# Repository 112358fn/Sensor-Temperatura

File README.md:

Sensor-Temperatura
==================

Medicion de temperatura mediante LM35 y PIC18F

Software:
=================
EAGLE
Version 7.1.0 for Linux
Light Edition
Freeware license for "non-profit"
and evaluation purposes

eagle-diff

Documentacion:
==================
Los datasheets de los componentes utilizados se encuentran en 
el directorio Doc/

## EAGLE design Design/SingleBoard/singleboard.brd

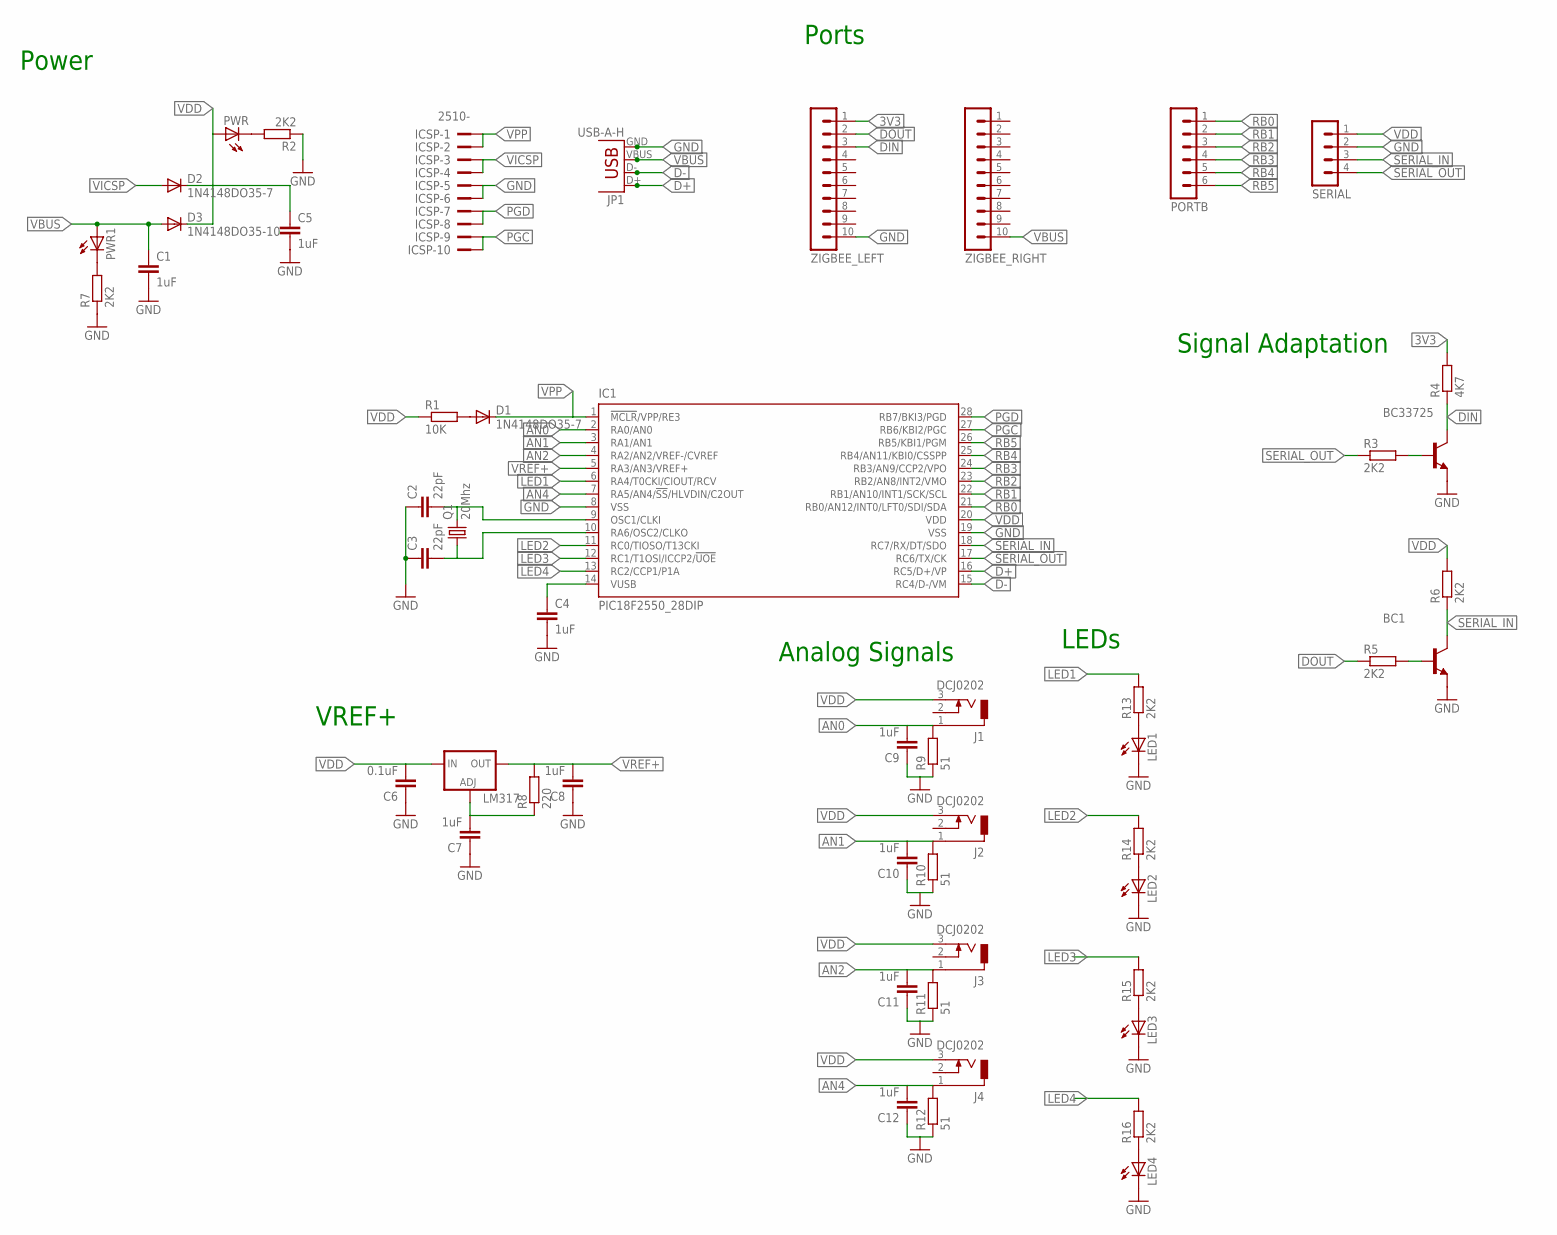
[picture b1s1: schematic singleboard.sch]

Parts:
BC1, BC33725: BC337-25-NPN-TO92-CBE; TO92-CBE
C1, C7, C8, C9, C10, C11, C12: 1uF; C050-025X075
C2, C3: 22pF; C025-024X044
C4, C5: 1uF; C025-024X044
C6: 0.1uF; C050-025X075
D1, D2: 1N4148DO35-7; DO35-7
D3: 1N4148DO35-10; DO35-10
IC1: PIC18F2550_28DIP; DIL28-3
ICSP: 2510-; PAK100/2500-10
J1, J2, J3, J4: DCJ0202
JP1: USB-A-H
LED1, LED2, LED3, LED4: LED3MM
LM317: LM317TS; 317TS
PORTB: MA06-1
PWR, PWR1: LED3MM
Q1: 20Mhz; HC49/S
R1: 10K; 0204/7
R2, R3, R5, R6, R7, R13, R14, R15, R16: 2K2; 0204/5
R4: 4K7; 0204/5
R8: 220; 0204/5
R9, R10, R11, R12: 51; 0204/5
SERIAL: MA04-1
ZIGBEE_LEFT: MA10-1
ZIGBEE_RIGHT: MA10-1

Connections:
3V3: R4.2, ZIGBEE_LEFT.1
AN0: C9.2, IC1.2 (RA0/AN0), J1.1, R9.2
AN1: C10.2, IC1.3 (RA1/AN1), J2.1, R10.2
AN2: C11.2, IC1.4 (RA2/AN2/VREF-/CVREF), J3.1, R11.2
AN4: C12.2, IC1.7 (RA5/AN4/!SS!/HLVDIN/C2OUT), J4.1, R12.2
D+: IC1.16 (RC5/D+/VP), JP1.D+
D-: IC1.15 (RC4/D-/VM), JP1.D-
DIN: BC33725.C, R4.1, ZIGBEE_LEFT.3
DOUT: R5.1, ZIGBEE_LEFT.2
GND: BC1.E, BC33725.E, C1.2, C2.1, C3.1, C4.2, C5.2, C6.1, C7.1, C8.1, C9.1, C10.1, C11.1, C12.1, IC1.8 (VSS), IC1.19 (VSS), ICSP.5, ICSP.6, JP1.GND, LED1.K (C), LED2.K (C), LED3.K (C), LED4.K (C), R2.1, R7.1, R9.1, R10.1, R11.1, R12.1, SERIAL.2, ZIGBEE_LEFT.10
LED1: IC1.6 (RA4/T0CKI/CIOUT/RCV), R13.2
LED2: IC1.11 (RC0/TIOSO/T13CKI), R14.2
LED3: IC1.12 (RC1/T1OSI/ICCP2/!UOE), R15.2
LED4: IC1.13 (RC2/CCP1/P1A), R16.2
unnamed: C3.2, IC1.10 (RA6/OSC2/CLKO), Q1.1
unnamed: D1.A, R1.2
unnamed: C4.1, IC1.14 (VUSB)
unnamed: C2.2, IC1.9 (OSC1/CLKI), Q1.2
unnamed: PWR.K (C), R2.2
unnamed: BC33725.B, R3.2
unnamed: BC1.B, R5.2
unnamed: PWR1.K (C), R7.2
unnamed: C7.2, LM317.1 (ADJ), R8.1
unnamed: LED1.A, R13.1
unnamed: LED2.A, R14.1
unnamed: LED3.A, R15.1
unnamed: LED4.A, R16.1
PGC: IC1.27 (RB6/KBI2/PGC), ICSP.9, ICSP.10
PGD: IC1.28 (RB7/BKI3/PGD), ICSP.7, ICSP.8
RB0: IC1.21 (RB0/AN12/INT0/LFT0/SDI/SDA), PORTB.1
RB1: IC1.22 (RB1/AN10/INT1/SCK/SCL), PORTB.2
RB2: IC1.23 (RB2/AN8/INT2/VMO), PORTB.3
RB3: IC1.24 (RB3/AN9/CCP2/VPO), PORTB.4
RB4: IC1.25 (RB4/AN11/KBI0/CSSPP), PORTB.5
RB5: IC1.26 (RB5/KBI1/PGM), PORTB.6
SERIAL_IN: BC1.C, IC1.18 (RC7/RX/DT/SDO), R6.1, SERIAL.3
SERIAL_OUT: IC1.17 (RC6/TX/CK), R3.1, SERIAL.4
VBUS: C1.1, D3.A, JP1.VBUS, PWR1.A, ZIGBEE_RIGHT.10
VDD: C5.1, C6.2, D2.C, D3.C, IC1.20 (VDD), J1.3, J2.3, J3.3, J4.3, LM317.3 (IN), PWR.A, R1.1, R6.2, SERIAL.1
VICSP: D2.A, ICSP.3, ICSP.4
VPP: D1.C, IC1.1 (!MCLR!/VPP/RE3), ICSP.1, ICSP.2
VREF+: C8.2, IC1.5 (RA3/AN3/VREF+), LM317.2 (OUT), R8.2

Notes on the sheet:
Ports
Power
Signal Adaptation
Analog Signals
LEDs
VREF+

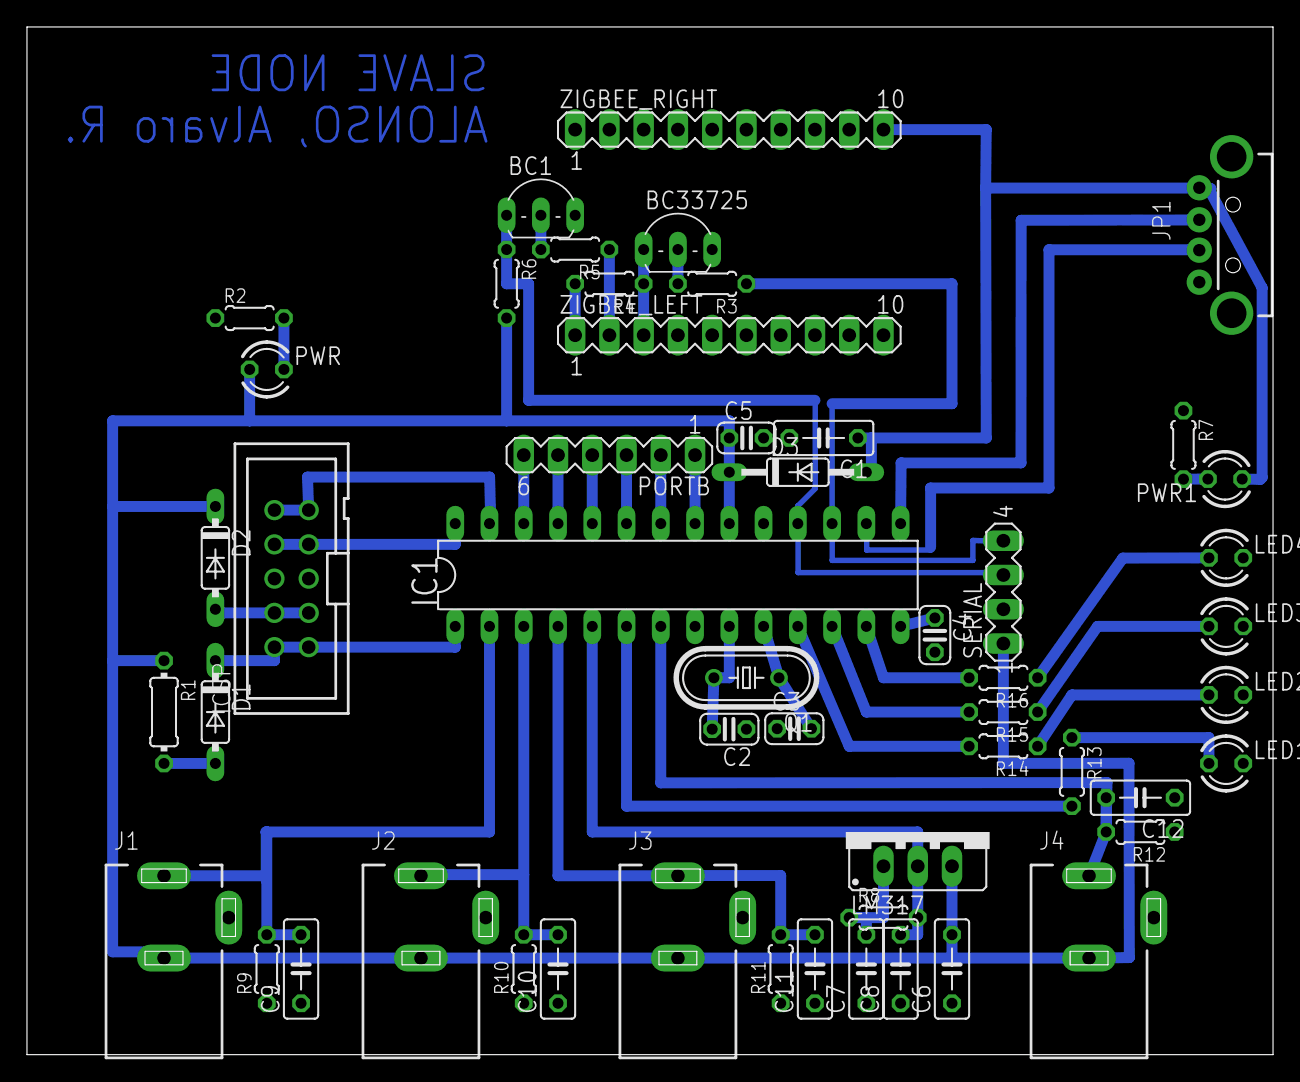
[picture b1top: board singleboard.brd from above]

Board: 2 copper layers, 92.4 x 76.2 mm, 52 parts (0 on the bottom side), 42 nets.

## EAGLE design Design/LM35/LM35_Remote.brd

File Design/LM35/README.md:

Seleccion:
==========
Se opta por seleccionar el sensor LM35 por ser un sensor
que nos entrega en valores de tension la temperatura en 
grados celcius.

Al contrario que el LM335 que mide la temperatura en 
grados Farenheit.

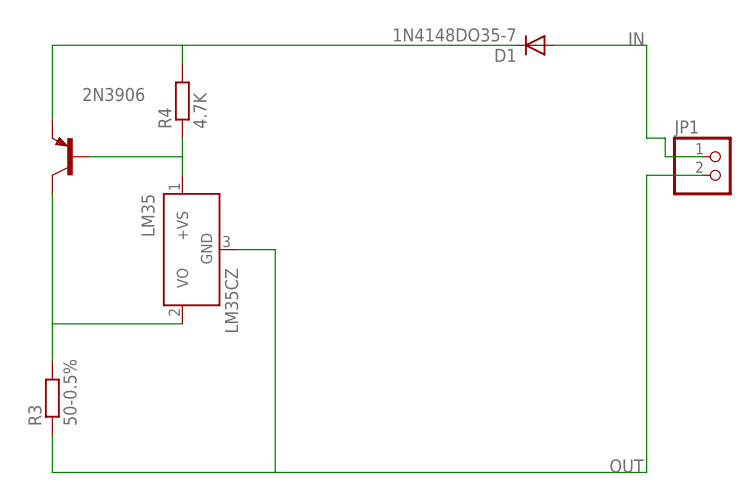
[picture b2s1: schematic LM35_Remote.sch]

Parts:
2N3906: 2N3906-PNP-TO92-EBC; TO92-EBC
D1: 1N4148DO35-7; DO35-7
JP1: PINHD-1X2; 1X02
LM35: LM35CZ; TO92
R3: 50-0.5%; 0207/7
R4: 4.7K; 0207/7

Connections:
IN: D1.A, JP1.1
unnamed: 2N3906.B, LM35.1 (+VS), R4.1
unnamed: 2N3906.C, LM35.2 (VO), R3.2
unnamed: 2N3906.E, D1.C, R4.2
OUT: JP1.2, LM35.3 (GND), R3.1

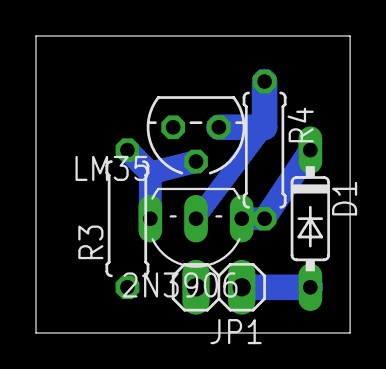
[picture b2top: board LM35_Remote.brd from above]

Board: 2 copper layers, 17.4 x 16.5 mm, 6 parts (0 on the bottom side), 5 nets.

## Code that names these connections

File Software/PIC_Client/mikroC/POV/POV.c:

// Timer0

int  _A[] = { 8,
 0b11000000,
 0b01110000,
 0b00101100,
 0b00100111,
 0b00111000,
 0b11100000,
 0b10000000,
 0b00000000,
};
int  _B[] = { 6,
 0b11111110,
 0b10010010,
 0b10010010,
 0b10010010,
 0b01111100,
 0b00000000,
};
int  _C[] = { 8,
 0b00010000,
 0b01101100,
 0b10000010,
 0b10000010,
 0b10000010,
 0b11000110,
 0b01000100,
 0b00000000,
};
int  _D[] = { 7,
 0b11111110,
 0b10000010,
 0b10000010,
 0b10000010,
 0b01000110,
 0b00111000,
 0b00000000,
};
int  _E[] = { 6,
 0b11111110,
 0b10010010,
 0b10010010,
 0b10010010,
 0b10010010,
 0b00000000,
};
int  _F[] = { 6,
 0b11111110,
 0b00010010,
 0b00010010,
 0b00010010,
 0b00000010,
 0b00000000,
};
int  _G[] = { 8,
 0b00010000,
 0b01111100,
 0b10000010,
 0b10000010,
 0b10010010,
 0b10010010,
 0b01110100,
 0b00000000,
};
int  _H[] = { 7,
 0b11111110,
 0b00010000,
 0b00010000,
 0b00010000,
 0b11111110,
 0b11111110,
 0b00000000,
};
int  _I[] = { 2,
 0b11111110,
 0b00000000,
};
int  _J[] = { 5,
 0b01000000,
 0b10000000,
 0b10000000,
 0b11111110,
 0b00000000,
};
int  _K[] = { 7,
 0b11111110,
 0b00010000,
 0b00011000,
 0b00100100,
 0b11000010,
 0b10000000,
 0b00000000,
};
int  _L[] = { 5,
 0b11111110,
 0b10000000,
 0b10000000,
 0b10000000,
 0b00000000,
};
int  _M[] = { 8,
 0b11111110,
 0b00011100,
 0b11100000,
 0b11000000,
 0b00111000,
 0b00011110,
 0b11111110,
 0b00000000,
};
int  _N[] = { 7,
 0b11111110,
 0b00001100,
 0b00011000,
 0b01100000,
 0b11111110,
 0b11111110,
 0b00000000,
};
int  _O[] = { 8,
 0b00010000,
 0b01101100,
 0b10000010,
 0b10000010,
 0b10000010,
 0b11000110,
 0b01111100,
 0b00000000,
};
int  _P[] = { 6,
 0b11111110,
 0b00010010,
 0b00010010,
 0b00010010,
 0b00011110,
 0b00000000,
};
int  _Q[] = { 9,
 0b00111000,
 0b01101100,
 0b10000010,
 0b10000010,
 0b11000010,
 0b11000110,
 0b11111100,
 0b10000000,
 0b00000000,
};
int  _R[] = { 7,
 0b11111110,
 0b00010010,
 0b00010010,
 0b00110010,
 0b11011110,
 0b10000000,
 0b00000000,
};
int  _S[] = { 7,
 0b01000000,
 0b11001110,
 0b10010010,
 0b10010010,
 0b10010010,
 0b01100100,
 0b00000000,
};
int  _T[] = { 7,
 0b00000010,
 0b00000010,
 0b00000010,
 0b11111110,
 0b00000010,
 0b00000010,
 0b00000000,
};
int  _U[] = { 7,
 0b01111110,
 0b10000000,
 0b10000000,
 0b10000000,
 0b11111110,
 0b00111110,
 0b00000000,
};
int  _V[] = { 8,
 0b00000010,
 0b00011100,
 0b01100000,
 0b11000000,
 0b00110000,
 0b00001110,
 0b00000010,
 0b00000000,
};
int  _W[] = { 11,
 0b00000110,
 0b00111100,
 0b11100000,
 0b11110000,
 0b00001110,
 0b00001110,
 0b11110000,
 0b11100000,
 0b00111110,
 0b00000010,
 0b00000000,
};
int  _X[] = { 7,
 0b10000010,
 0b01000110,
 0b00101100,
 0b00111000,
 0b01100100,
 0b11000010,
 0b00000000,
};
int  _Y[] = { 7,
 0b00000010,
 0b00000100,
 0b00011000,
 0b11110000,
 0b00001100,
 0b00000010,
 0b00000000,
};
int  _Z[] = { 7,
 0b10000001,
 0b11100011,
 0b10110011,
 0b10011011,
 0b10000111,
 0b10000011,
 0b00000000,
};

int  ss[] = { 6,
 0b00000000,
 0b00000000,
 0b00000000,
 0b00000000,
 0b00000000,
 0b00000000,
};

//int* Msg[] = {_L,ss,_A,ss,_V,ss,_E,ss,_R,ss,_I,ss,_T,ss,_E,ss};
int* Msg[] = {_A,ss,_L,ss,_V,ss,_I,ss};
int MsgLen = 8;

unsigned char stateON=1;

void init(void){
// Initialize PIC: Configuration
//OSCCON = 0x61;
//Port A
TRISA.RA0 = 0;
TRISA.RA1 = 0;
TRISA.RA2 = 0;
TRISA.RA3 = 0;
TRISA.RA4 = 0;
TRISA.RA5 = 0;
//Port C
TRISC.RC0 = 0;
TRISC.RC1 = 0;
//Timer 0
T0CON.TMR0ON = 0; //Off
T0CON.T08BIT = 0; //16 bit
T0CON.T0CS = 0;//Internal instruction cycle clock (CLKO)
T0CON.T0SE = 0;//Rising Edge
T0CON.PSA = 0;//Timer0 clock input comes from prescaler output.
T0CON.T0PS2 = 0; //Prescaler 8
T0CON.T0PS1 = 1;
T0CON.T0PS0 = 0;
//Interrupts
INTCON.GIE = 1;//Global Interrupt Enable
INTCON.PEIE = 0;//Peripheral Interrupt Disable
INTCON.INT0IE = 0;//INT0 External Interrupt Disable
INTCON.TMR0IE = 1;//TMR0 Overflow Interrupt Enable

return;
}


void printLetter(int * letter){
  int i;
  for(i=1; i<letter[0]; i++){
   PORTA = letter[i] & 0x3F;
   PORTC = (letter[i]&0xC0)>>6;
   delay_ms(3);//Ancho letra
  }
  
return;
}

void interrupt(void){
int i;
// Disable Timer0 interrupts
INTCON.TMR0IE = 0;//TMR0 Overflow Interrupt Enable
//Verify Timer0 Overfload Flag
if(INTCON.TMR0IF){
  for(i=0; i<MsgLen; i++)printLetter(Msg[i]);
}
//Clear Timer0 Overfload Flag
INTCON.TMR0IF = 0;
//Re-enable Timer0 interrupts
INTCON.TMR0IE = 1;//TMR0 Overflow Interrupt Enable
}



void main(){
int i;
init();
//Start timer0
T0CON.TMR0ON = 1; //On
while(1){};
return;
}

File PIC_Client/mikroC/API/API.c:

#include "Zigbee_API_Simple.h"
#include "API.h"
volatile unsigned char ch=0,connect=FALSE, zigbee_id=0;
volatile unsigned int presc=0,sample_time=10;

void main(void){
     init();
     delay_ms(200);
     connect=FALSE;
     T0CON.TMR0ON = 1; //Start timer0
     while(1){}
     return;
}


void
send_AD_result(void){
    char buffer[4];
    
    //Read A/D result
    buffer[0]=zigbee_id;
    buffer[1]=ch;
    buffer[2]=ADRESH;
    buffer[3]=ADRESL;
    //Send Transmit request
    send(buffer,4);
    //Change ennable Channel
    turn_off_leds;
    ch++;
    if(ch>=4)ch=0;
    switch(ch){
     case 0:if(ADC_channel_EN[0]){channel0;break;}
     case 1:if(ADC_channel_EN[1]){channel1;break;}
     case 2:if(ADC_channel_EN[2]){channel2;break;}
     case 3:if(ADC_channel_EN[3]){channel4;break;}
            else if(ADC_channel_EN[0]){channel0;break;}
    }
    return;
}

void
read_ZB_frame(void){
    int length;
    //Start indicator
    if(RCREG == 0x7E)length=receive_frame(buf);
    else return;
    //Try to decode
    if(decode_API_frame(buf,length)!=NULL){
       //Use the information
       switch(my_data.cmdID){
       //Received data
       case ZBRECVPCK:
            length=get_ZBRCV_packet_data(&my_data,buf);
            actions(buf, length);
            break;
       case ATRESPONSE:
            if(get_AT_response_status(&my_data)==ATOK){}
            else {connect=FALSE;handshake();}
       default:break;
            
       }
    }
    return;

}

void
actions(unsigned char * buf, unsigned char length){
    switch(buf[0]){
      case 'S': //Set channel to ennable
         if(length>=4){enable_channel(buf);
            send("SOK",3);
            }
         break;
      case 'T'://Set sample time in sec
        if(length>=3){sample_time=((buf[1]<<8)|buf[2]);
            send("TOK",3);
            }
        break;
      case 'H'://Handshake
        if(length>=2){
            zigbee_id=buf[1];
            connect=TRUE;
            send("HOK",3);
            }
        break;
      default:
         send("Received something else",23);
         break;
    }
    return;
}



void
init(void){
     //EUART init
     TRISC = 0b11000000;
     PORTC.RC0 = 0;
     PORTC.RC1 = 0;
     PORTC.RC2 = 0;
     PORTC.RC4 = 0;
     PORTC.RC5 = 0;
     UART1_Init(9600);
     BAUDCON.TXCKP = 1; //Tx Data is inverted
     BAUDCON.RXDTP = 1; //Rx Data is inverted
     Delay_ms(100);

     //ADC
     TRISA = 0b00101111;
     PORTA.RA4=0;
     //  Configure analog pins, voltage reference and digital I/O (ADCON1)
     ADCON1.VCFG1 = 0;//VSS REFERENCE
     ADCON1.VCFG0 = 1;//AN3 REFERENCE
     ADCON1.PCFG3 = 1;//AN0-4 analog input
     ADCON1.PCFG2 = 0;
     ADCON1.PCFG1 = 1;
     ADCON1.PCFG0 = 0;
     //  Select A/D input channel (ADCON0)
     channel0;
     //  Select A/D acquisition time (ADCON2)
     ADCON2.ACQT2 = 0; //2Tad
     ADCON2.ACQT1 = 0;
     ADCON2.ACQT0 = 1;
     //  Select A/D conversion clock (ADCON2)
     ADCON2.ADCS2 = 1; //64Tosc
     ADCON2.ADCS1 = 1;
     ADCON2.ADCS0 = 0;
     // A/D Result Format Select bit
     ADCON2.ADFM = 1;
     //  Turn on A/D module (ADCON0)
     ADCON0.ADON = 1;
     //Turn off indicator LEDs
     turn_off_leds;

     //Timer 0
     T0CON.TMR0ON = 0; //Off
     T0CON.T08BIT = 0; //16 bit
     T0CON.T0CS = 0;//Internal instruction cycle clock (CLKO)
     T0CON.T0SE = 0;//Rising Edge
     T0CON.PSA = 0;//Timer0 clock input comes from prescaler output.
     T0CON.T0PS2 = 1; //Prescaler 64
     T0CON.T0PS1 = 0;
     T0CON.T0PS0 = 1;
     //In sec=50ns*256*2^16*4=0.84s
    //Interrupts
    //  PERIPHERAL INTERRUPT REQUEST
    PIR1.ADIF = 0;//Clear A/D Conversion Flag
    PIR1.RCIF = 0;//The EUSART receive buffer(RCREG) is empty
    INTCON.TMR0IF = 0;//TMR0 register did not overflow
    //  PERIPHERAL INTERRUPT ENABLE
    PIE1.ADIE = 1;//Enables the A/D interrupt
    PIE1.RCIE = 1;//Enables the EUSART receive interrupt
    //   PERIPHERAL INTERRUPT PRIORITY REGISTER
    IPR1.ADIP = 0;//A/D Converter Interrupt Priority bit LOW
    IPR1.RCIP = 1;//EUSART Receive Interrupt Priority bit HIGH
    INTCON.TMR0IP = 0;//TMR0 Overflow Interrupt Priority bit LOW
    //   RESET CONTROL REGISTER
    RCON.IPEN = 1;//Enable priority levels on interrupts
    //   INTERRUPT CONTROL REGISTER
    INTCON.GIEH = 1;//Enables all high-priority interrupts
    INTCON.GIEL = 1;//Enables all low-priority peripheral interrupts (if GIE/GIEH = 1)
    INTCON.TMR0IE = 1;//TMR0 Overflow Interrupt Enable

    //API Frame functions
    ATCMD_init();//AT commands structure to generate API frames
    ZBTR_init(addr64,addr16);//Transmit structure to generate API frames
    RATCMD_init(addr64,addr16);//Remote AT to generate API frames

    return;
}


void
interrupt(void){
     int i, sum=0;
     
   //Verify Timer0 Overfload Flag
  if(INTCON.TMR0IF){
    // Disable Timer0 interrupts
    INTCON.TMR0IE = 0;//TMR0 Overflow Interrupt Enable
    //First start
    if(connect!=TRUE)handshake();
    else if(connect==TRUE){
      //No channel Enable
      for(i=0;i<4;i++)sum+=ADC_channel_EN[i];
      if(sum==0)ADCON0.GO=0;
      else my_prescaler();
      }
    //Clear Timer0 Overfload Flag
    INTCON.TMR0IF = 0;
    //Re-enable Timer0 interrupts
    INTCON.TMR0IE = 1;//TMR0 Overflow Interrupt Enable
    return;
  }
  
  //Verify an A/D conversion completed
  if(PIR1.ADIF){
    //Disable A/D interrupts
    INTCON.GIEL = 0;//Disables all low-priority peripheral interrupts
    //Send the conversion result
    send_AD_result();
    //Clear A/D Conversion Flag
    PIR1.ADIF = 0;
    //Re-enable A/D interrupts
    INTCON.GIEL = 1;//Enables all low-priority peripheral interrupts
    return;
  }
  
  //Verify RC Euart reception
  if(PIR1.RCIF){
    //Disable RC interrupts
    INTCON.GIEH = 0;//Disables all interrupts
    //Read frame
    read_ZB_frame();
    //Clear RC Conversion Flag
    PIR1.RCIF = 0;
    //Re-enable RC interrupts
    INTCON.GIEH = 1;//Enables all high-priority interrupts
    return;
  }
 return;
}

int
receive_frame(unsigned char * buf){
     int i,length;
     buf[0]=0x7E;
     for(i=1;i<3;i++){
        while(!UART1_Data_Ready()){};
        buf[i]=UART_Read();
     }
     length=(((unsigned int)buf[1])<< 8)|((unsigned int)buf[2]);
     for(i=3;i<length+4;i++){
        while(!UART1_Data_Ready()){}
        buf[i]=UART_Read();
     }
     return length+4;
}

void
send(unsigned char * buf, unsigned char len){
    int i;
    _zbtr;
    API_frame=_zbtr.request(buf,len);
    for(i=0;i<API_frame_length(API_frame); i++)
       UART1_Write(API_frame[i]);
}
void
my_prescaler(void){//Multiples of 0.84seconds
  presc++;
  if(presc>=(sample_time*100/84)){
    ADCON0.GO = 1;//RE-Start Conversion
    presc=0;}
  return;
}
    
void
handshake(void){
     int i;
     unsigned char buf[3];
    _atcmd;
    if(connect==FALSE){
      buf[0]='C';
      buf[1]='B';
      buf[2]=1;
      API_frame=_atcmd.request(buf,3);
      for(i=0;i<API_frame_length(API_frame); i++)
         UART1_Write(API_frame[i]);
      connect=WAIT;
    }
    else if(connect==WAIT){
      presc++;
      if(presc>=10){
        connect = FALSE;//RE-Start Connection
       presc=0;}
    }
      
      
}
    /*while(1){
            while(!UART1_Data_Ready()){}
            if(RCREG == 0x7E){
               length=receive_frame(buf);
               data_=decode_API_frame(buf,n);
                   _zbtr;
                   API_frame=_zbtr.request((data_->cmdID),1);
                   for(i=0;i<API_frame_length(API_frame); i++)
                      UART1_Write(API_frame[i]);
            }

            if(RCREG == 'A'){
                 zbtr_;
                 API_frame=zbtr_->request("FUNCIONA?",9);
            }
            else if(RCREG == 'B'){
                 atcmd_;
                 API_frame=atcmd_->request("IDHOLA",6);
            }
            else{
                 ratcmd_;
                 API_frame=ratcmd_->request("IDHOLA",6);
            }
            for(i=0;i<API_frame_length(API_frame); i++)
                 UART1_Write(API_frame[i]);
     }*/

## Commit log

2014-09-01 Agregada documentacion de los sensores de temp disponibles
2014-09-02 Explicacion de la seleccion del sensor LM35
2014-09-02 Agregado Latex para diario de desarrollo
2014-09-02 Informe del dia 1 de Septiembre
2014-09-02 Informe sobre 2 de Septiembre
2014-09-03 Trabajo realizado el dia miercoles 3 septiembre
2014-09-04 Daily Log del dia
2014-09-04 Modificado el diseno de la placa del sensor
2014-09-06 Ultima revision del resumen semanal
2014-09-08 Seleccion de un microcontrolador
2014-09-08 Agregada documentacion del PIC16F884 y sensor de corriente
2014-09-08 Agregado gitattirbutes para evitar diff del xml de Eagle
2014-09-08 Eliminado archivo de Kile .kilepr
2014-10-27 Retomando el trabajo - Desarrollo del servidor C
2014-12-17 Ultima modificacion plaqueta sensor
2014-12-17 Pequeñas modificaciones en el conector jack
2015-04-24 Fix Doc files
2015-04-24 Add new doc files
2015-04-24 Add PIC Programs
2015-04-24 Added backup firmwares of Xbee
2015-04-24 Config Docs
2015-04-24 PIC client side codes: MikroC
2015-04-24 Move all software to folder
2015-04-24 Add web app, Front End
2015-11-03 Eliminacion documentacion innecesaria
2015-11-03 Movido archivo de configuracion de beagleBone
2015-11-03 Eliminado diario de desarrollo
2015-11-03 Removidos proyectos MikroC innecesarios
2015-11-03 Eliminado codigo innecesario
2015-11-03 Agregado backend C

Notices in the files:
parts and their libraries:
SparkFun-Connectors: Licensing: Creative Commons ShareAlike 4.0 International - https://creativecommons.org/licenses/by-sa/4.0
